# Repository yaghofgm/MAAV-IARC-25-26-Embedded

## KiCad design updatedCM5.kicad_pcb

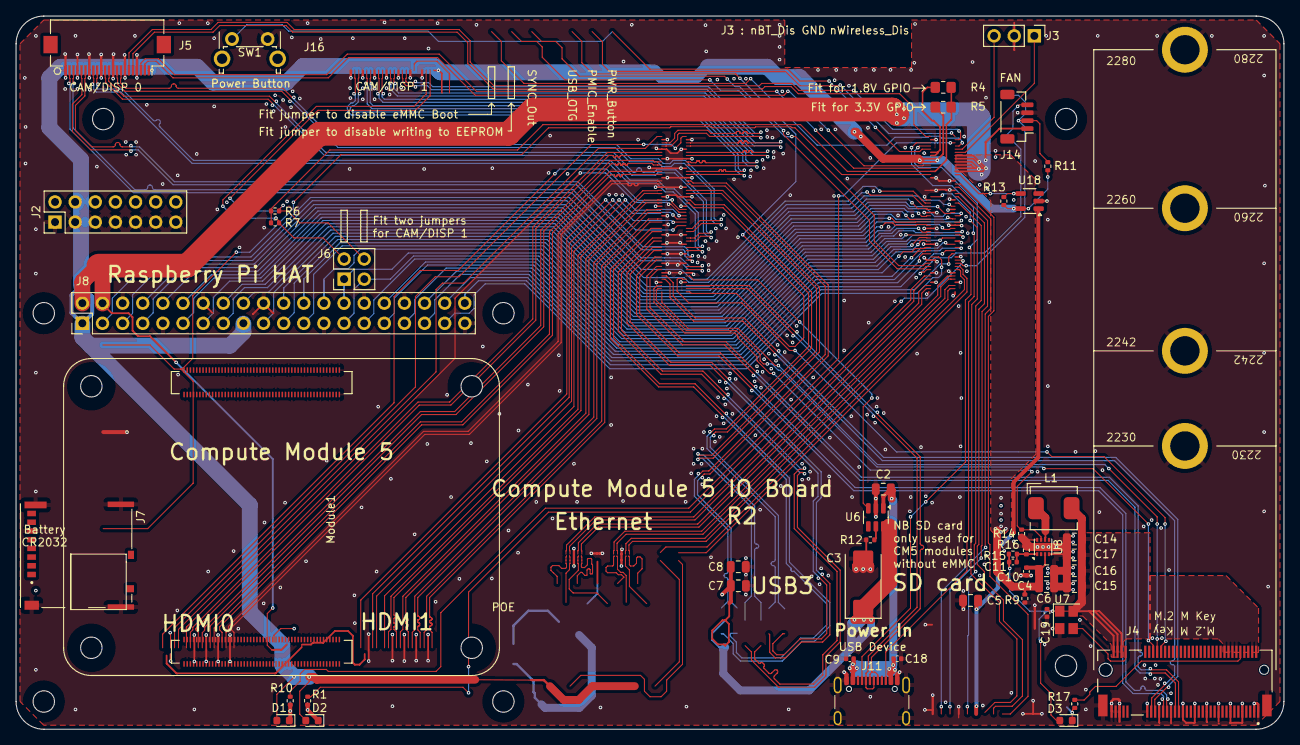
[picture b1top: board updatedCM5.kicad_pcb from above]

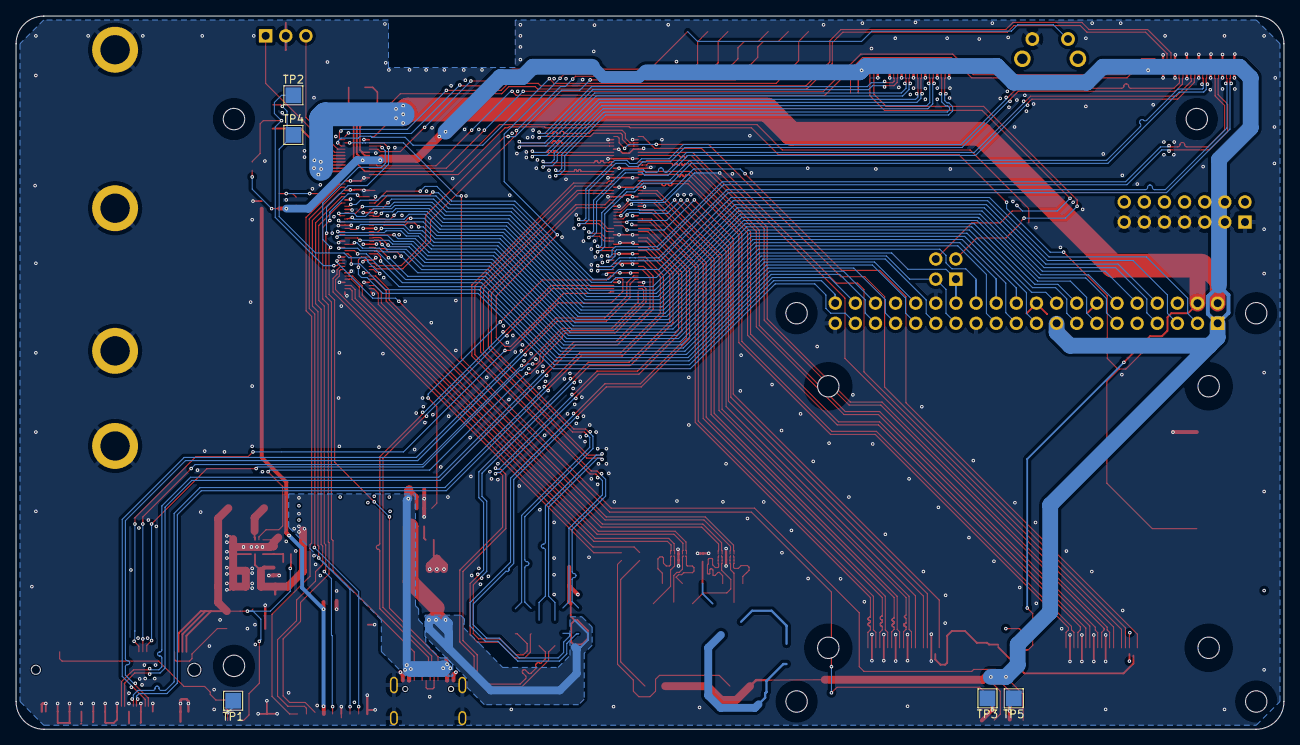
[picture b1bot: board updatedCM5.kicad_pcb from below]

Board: 4 copper layers, 160.0 x 90.0 mm, 61 parts (5 on the bottom side), 94 nets.

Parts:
C2, C4, C5, C6, C7, C8, C14, C15, C16, C17: 10u; C_0805_2012Metric
C3: 100uF; CP_EIA-7343-31_Kemet-D
C9, C10, C18, C19: 100n; C_0402_1005Metric
C11: 4.7nF; C_0402_1005Metric
D1: LED Red; LED_0603_1608Metric
D2, D3: LED Green; LED_0603_1608Metric
H2, H3, H4, H5, H6, H7, H8: MountingHole; MountingHole_2.7mm_M2.5_DIN965
J2: Conn_02x07_Odd_Even; PinHeader_2x07_P2.54mm_Vertical
J3: Conn_01x03; PinHeader_1x03_P2.54mm_Vertical
J4: Bus_M.2_Socket_M; M.2 M Key socket
J5: Conn_01x22_Female; Hirose_FH12-22S-0.5SH_1x22-1MP_P0.50mm_Horizontal
J6: THD-02-R; PinHeader_2x02_P2.54mm_Vertical
J7: Micro_SD_Card_Det; SDCARD_MOLEX_503398-1892
J8: THD-20-R; PinHeader_2x20_P2.54mm_Vertical
J11: USB_C_Receptacle_USB2.0; USB_C_Receptacle_GCT_USB4105-xx-A_16P_TopMnt_Horizontal
J14: JST_SHBM04B-SRSS-TB; JST_SH_BM04B-SRSS-TB_1x04-1MP_P1.00mm_Vertical
L1: 2.2uH; L_Bourns_SRP5030CC
Module1: ComputeModule5-CM5; Raspberry-Pi-5-Compute-Module
R1, R10, R17: 1k; R_0402_1005Metric
R4: nf; R_0805_2012Metric_Pad1.20x1.40mm_HandSolder
R5: 0R; R_0805_2012Metric_Pad1.20x1.40mm_HandSolder
R6, R7, R9, R16: 2.2K 1%; R_0402_1005Metric
R11, R13, R15: 10K 1%; R_0402_1005Metric
R12: 15K 1%; R_0402_1005Metric
R14: 100K 1%; R_0402_1005Metric
SW1: Right angle Tact button; SW_Tactile_SPST_Angled_PTS645Vx58-2LFS
TP1, TP2, TP3, TP4, TP5: TestPoint; TestPoint_Pad_2.0x2.0mm
U6: AP22653W6; SOT-23-6
U7: ASEK-32.768KHZ-L-R-T; Crystal_SMD_3225-4Pin_3.2x2.5mm
U8: AP3441SHE-7B; DFN-8-1EP_2x2mm_P0.5mm_EP1.05x1.75mm
U18: RT9742GGJ5; SOT-23-5

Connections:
/+3.3v: D1.2 (A), D2.2 (A), J5.22, J8.1, J8.17, Module1.84 (+3.3v_(Output)), Module1.86 (+3.3v_(Output)), R5.1, R11.1, R13.1, U18.5 (IN)
/+5v: C2.1, C4.1, C6.1, C9.1, C10.1, C18.1, J8.2, J8.4, J11.A4 (VBUS), J11.A9 (VBUS), J11.B4 (VBUS), J11.B9 (VBUS), J14.1, Module1.77 (+5v_(Input)), Module1.79 (+5v_(Input)), Module1.81 (+5v_(Input)), Module1.83 (+5v_(Input)), Module1.85 (+5v_(Input)), Module1.87 (+5v_(Input)), R9.1, U6.1 (IN), U8.3 (VIN)
/CC1: J11.A5 (CC1), Module1.94 (CC1)
/CC2: J11.B5 (CC2), Module1.96 (CC2)
/CM5_GPIO ( Ethernet, GPIO, SDCARD)/+1.8v: Module1.88 (+1.8v_(Output)), Module1.90 (+1.8v_(Output)), R4.1
/CM5_GPIO ( Ethernet, GPIO, SDCARD)/BT_nDis: J3.3, Module1.91 (BT_nDisable)
/CM5_GPIO ( Ethernet, GPIO, SDCARD)/CAM_GPIO0: J5.17, Module1.97 (CAM_GPIO0)
/CM5_GPIO ( Ethernet, GPIO, SDCARD)/CAM_GPIO1: J5.18, Module1.100 (CAM_GPIO1)
/CM5_GPIO ( Ethernet, GPIO, SDCARD)/EEPROM_nWP: J2.4, Module1.20 (EEPROM_nWP)
/CM5_GPIO ( Ethernet, GPIO, SDCARD)/GPIO2: J8.3, Module1.58 (GPIO2)
/CM5_GPIO ( Ethernet, GPIO, SDCARD)/GPIO3: J8.5, Module1.56 (GPIO3)
/CM5_GPIO ( Ethernet, GPIO, SDCARD)/GPIO4: J8.7, Module1.54 (GPIO4)
/CM5_GPIO ( Ethernet, GPIO, SDCARD)/GPIO5: J8.29, Module1.34 (GPIO5)
/CM5_GPIO ( Ethernet, GPIO, SDCARD)/GPIO6: J8.31, Module1.30 (GPIO6)
/CM5_GPIO ( Ethernet, GPIO, SDCARD)/GPIO7: J8.26, Module1.37 (GPIO7)
/CM5_GPIO ( Ethernet, GPIO, SDCARD)/GPIO8: J8.24, Module1.39 (GPIO8)
/CM5_GPIO ( Ethernet, GPIO, SDCARD)/GPIO9: J8.21, Module1.40 (GPIO9)
/CM5_GPIO ( Ethernet, GPIO, SDCARD)/GPIO10: J8.19, Module1.44 (GPIO10)
/CM5_GPIO ( Ethernet, GPIO, SDCARD)/GPIO11: J8.23, Module1.38 (GPIO11)
/CM5_GPIO ( Ethernet, GPIO, SDCARD)/GPIO12: J8.32, Module1.31 (GPIO12)
/CM5_GPIO ( Ethernet, GPIO, SDCARD)/GPIO13: J8.33, Module1.28 (GPIO13)
/CM5_GPIO ( Ethernet, GPIO, SDCARD)/GPIO14: J8.8, Module1.55 (GPIO14)
/CM5_GPIO ( Ethernet, GPIO, SDCARD)/GPIO15: J8.10, Module1.51 (GPIO15)
/CM5_GPIO ( Ethernet, GPIO, SDCARD)/GPIO16: J8.36, Module1.29 (GPIO16)
/CM5_GPIO ( Ethernet, GPIO, SDCARD)/GPIO17: J8.11, Module1.50 (GPIO17)
/CM5_GPIO ( Ethernet, GPIO, SDCARD)/GPIO18: J8.12, Module1.49 (GPIO18)
/CM5_GPIO ( Ethernet, GPIO, SDCARD)/GPIO19: J8.35, Module1.26 (GPIO19)
/CM5_GPIO ( Ethernet, GPIO, SDCARD)/GPIO20: J8.38, Module1.27 (GPIO20)
/CM5_GPIO ( Ethernet, GPIO, SDCARD)/GPIO21: J8.40, Module1.25 (GPIO21)
/CM5_GPIO ( Ethernet, GPIO, SDCARD)/GPIO22: J8.15, Module1.46 (GPIO22)
/CM5_GPIO ( Ethernet, GPIO, SDCARD)/GPIO23: J8.16, Module1.47 (GPIO23)
/CM5_GPIO ( Ethernet, GPIO, SDCARD)/GPIO24: J8.18, Module1.45 (GPIO24)
/CM5_GPIO ( Ethernet, GPIO, SDCARD)/GPIO25: J8.22, Module1.41 (GPIO25)
/CM5_GPIO ( Ethernet, GPIO, SDCARD)/GPIO26: J8.37, Module1.24 (GPIO26)
/CM5_GPIO ( Ethernet, GPIO, SDCARD)/GPIO27: J8.13, Module1.48 (GPIO27)
/CM5_GPIO ( Ethernet, GPIO, SDCARD)/GPIO_VREF: Module1.78 (GPIO_VREF(1.8v/3.3v_Input)), R4.2, R5.2, R6.1, R7.1
/CM5_GPIO ( Ethernet, GPIO, SDCARD)/ID_SC: J6.1, J8.28, Module1.35 (ID_SC)
/CM5_GPIO ( Ethernet, GPIO, SDCARD)/ID_SD: J6.3, J8.27, Module1.36 (ID_SD)
/CM5_GPIO ( Ethernet, GPIO, SDCARD)/PMIC_ENABLE: J2.12, Module1.99 (PMIC_ENABLE)
/CM5_GPIO ( Ethernet, GPIO, SDCARD)/PWM: J14.2, Module1.19 (FAN_PWM), R11.2, TP2.1
/CM5_GPIO ( Ethernet, GPIO, SDCARD)/PWR_BUT: J2.14, Module1.92 (PWR_BUT), SW1.1
/CM5_GPIO ( Ethernet, GPIO, SDCARD)/SD_CLK: J7.5 (CLK), Module1.57 (SD_CLK)
/CM5_GPIO ( Ethernet, GPIO, SDCARD)/SD_CMD: J7.3 (CMD), Module1.62 (SD_CMD)
/CM5_GPIO ( Ethernet, GPIO, SDCARD)/SD_DAT0: J7.7 (DAT0), Module1.63 (SD_DAT0)
/CM5_GPIO ( Ethernet, GPIO, SDCARD)/SD_DAT1: J7.8 (DAT1), Module1.67 (SD_DAT1)
/CM5_GPIO ( Ethernet, GPIO, SDCARD)/SD_DAT2: J7.1 (DAT2), Module1.69 (SD_DAT2)
/CM5_GPIO ( Ethernet, GPIO, SDCARD)/SD_DAT3: J7.2 (DAT3/CD), Module1.61 (SD_DAT3)
/CM5_GPIO ( Ethernet, GPIO, SDCARD)/SD_PWR: C5.1, J7.4 (VDD), U18.1 (OUT)
/CM5_GPIO ( Ethernet, GPIO, SDCARD)/SD_PWR_ON: Module1.75 (SD_PWR_ON), R13.2, U18.4 (EN)
/CM5_GPIO ( Ethernet, GPIO, SDCARD)/SYNC_OUT: J2.6, Module1.18 (Ethernet_SYNC_OUT(3.3v))
/CM5_GPIO ( Ethernet, GPIO, SDCARD)/TACHO: J14.4, Module1.16 (FAN_TACHO), TP4.1
/CM5_GPIO ( Ethernet, GPIO, SDCARD)/USBOTG: J2.10, Module1.101 (USB_OTG_ID)
/CM5_GPIO ( Ethernet, GPIO, SDCARD)/WL_nDis: J3.1, Module1.89 (WiFi_nDisable)
/CM5_GPIO ( Ethernet, GPIO, SDCARD)/nPWR_LED: Module1.95 (LED_nPWR), R10.2
/CM5_GPIO ( Ethernet, GPIO, SDCARD)/nRPIBOOT: J2.2, Module1.93 (nRPIBOOT)
/CM5_HighSpeed/DPHY0_C_N: J5.8, Module1.127 (MIPI0_C_N)
/CM5_HighSpeed/DPHY0_C_P: J5.9, Module1.129 (MIPI0_C_P)
/CM5_HighSpeed/DPHY0_D0_N: J5.2, Module1.115 (MIPI0_D0_N)
/CM5_HighSpeed/DPHY0_D0_P: J5.3, Module1.117 (MIPI0_D0_P)
/CM5_HighSpeed/DPHY0_D1_N: J5.5, Module1.121 (MIPI0_D1_N)
/CM5_HighSpeed/DPHY0_D1_P: J5.6, Module1.123 (MIPI0_D1_P)
/CM5_HighSpeed/DPHY0_D2_N: J5.11, Module1.133 (MIPI0_D2_N)
/CM5_HighSpeed/DPHY0_D2_P: J5.12, Module1.135 (MIPI0_D2_P)
/CM5_HighSpeed/DPHY0_D3_N: J5.14, Module1.139 (MIPI0_D3_N)
/CM5_HighSpeed/DPHY0_D3_P: J5.15, Module1.141 (MIPI0_D3_P)
/CM5_HighSpeed/PCIE_CLK_N: J4.53 (REFCLKn), Module1.112 (PCIe_CLK_N)
/CM5_HighSpeed/PCIE_CLK_P: J4.55 (REFCLKp), Module1.110 (PCIe_CLK_P)
/CM5_HighSpeed/PCIE_PWR_EN: Module1.106 (PCIE_PWR_EN), R14.1, U8.7 (EN)
/CM5_HighSpeed/PCIE_RX_N: J4.43 (PETp0), Module1.118 (PCIe_RX_N)
/CM5_HighSpeed/PCIE_RX_P: J4.41 (PETn0), Module1.116 (PCIe_RX_P)
/CM5_HighSpeed/PCIE_TX_N: J4.49 (PERp0), Module1.124 (PCIe_TX_N)
/CM5_HighSpeed/PCIE_TX_P: J4.47 (PERn0), Module1.122 (PCIe_TX_P)
/CM5_HighSpeed/PCIE_nCLKREQ: J4.52 (~CLKREQ), Module1.102 (PCIe_nCLKREQ)
/CM5_HighSpeed/PCIE_nRST: J4.50 (~PERST), Module1.109 (PCIe_nRST)
/CM5_HighSpeed/PCIE_nWAKE: J4.54 (~PEWAKE), Module1.104 (PCIE_nWAKE)
/CM5_HighSpeed/SCL0: J5.20, Module1.80 (SCL0)
/CM5_HighSpeed/SCL1: J6.2, R7.2
/CM5_HighSpeed/SDA0: J5.21, Module1.82 (SDA0)
/CM5_HighSpeed/SDA1: J6.4, R6.2
/CM5_HighSpeed/VBUS: C3.1, C7.1, C8.1, U6.6 (OUT)
/CM5_HighSpeed/VBUS_EN: Module1.111 (VBUS_EN), U6.3 (EN)
/PCIe-M2/FB: C11.2, R15.2, R16.1, U8.1 (FB)
/PCIe-M2/M2_3v3: C11.1, C14.1, C15.1, C16.1, C17.1, C19.1, D3.2 (A), J4.2 (3.3V), J4.4 (3.3V), J4.12 (3.3V), J4.14 (3.3V), J4.16 (3.3V), J4.18 (3.3V), J4.70 (3.3V), J4.72 (3.3V), J4.74 (3.3V), L1.2, R15.1, U7.1 (EN), U7.4 (VDD)
/USB2_N: J11.A7 (D-), J11.B7 (D-), Module1.103 (USB2_N)
/USB2_P: J11.A6 (D+), J11.B6 (D+), Module1.105 (USB2_P)
GND: C2.2, C3.2, C4.2, C5.2, C6.2, C7.2, C8.2, C9.2, C10.2, C14.2, C15.2, C16.2, C17.2, C18.2, C19.2, J2.1, J2.3, J2.5, J2.7, J2.9, J2.11, J2.13, J3.2, J4.1 (GND), J4.3 (GND), J4.9 (GND), J4.15 (GND), J4.21 (GND), J4.27 (GND), J4.33 (GND), J4.39 (GND), J4.45 (GND), J4.51 (GND), J4.57 (GND), J4.71 (GND), J4.73 (GND), J4.75 (GND), J4.M1 (GND2230), J4.M2 (GND2242), J4.M3 (GND2260), J4.M4 (GND2280), J4.S1, J4.S2, J5.1, J5.4, J5.7, J5.10, J5.13, J5.16, J5.19, J7.6 (VSS), J7.11 (SHIELD), J8.6, J8.9, J8.14, J8.20, J8.25, J8.30, J8.34, J8.39, J11.A1 (GND), J11.A12 (GND), J11.B1 (GND), J11.B12 (GND), J11.S1 (SHIELD), J14.3, Module1.1 (GND), Module1.2 (GND), Module1.7 (GND), Module1.8 (GND), Module1.13 (GND), Module1.14 (GND), Module1.22 (GND), Module1.23 (GND), Module1.32 (GND), Module1.33 (GND), Module1.42 (GND), Module1.43 (GND), Module1.52 (GND), Module1.53 (GND), Module1.59 (GND), Module1.60 (GND), Module1.65 (GND), Module1.66 (GND), Module1.71 (GND), Module1.74 (GND), Module1.98 (GND), Module1.107 (GND), Module1.108 (GND), Module1.113 (GND), Module1.114 (GND), Module1.119 (GND), Module1.120 (GND), Module1.125 (GND), Module1.126 (GND), Module1.131 (GND), Module1.132 (GND), Module1.137 (GND), Module1.138 (GND), Module1.144 (GND), Module1.150 (GND), Module1.155 (GND), Module1.156 (GND), Module1.161 (GND), Module1.162 (GND), Module1.167 (GND), Module1.168 (GND), Module1.173 (GND), Module1.174 (GND), Module1.179 (GND), Module1.180 (GND), Module1.185 (GND), Module1.186 (GND), Module1.191 (GND), Module1.192 (GND), Module1.197 (GND), Module1.198 (GND), R9.2, R12.2, R14.2, R16.2, SW1.2, U6.2 (GND), U7.2 (GND), U8.4 (PGND), U8.8 (SGND), U8.9 (PAD), U18.2 (GND)
unnamed: D1.1 (K), R10.1, TP5.1
unnamed: D2.1 (K), R1.1, TP3.1
unnamed: D3.1 (K), R17.1, TP1.1
unnamed: J4.10 (DAS/~DSS/~LED1), R17.2
unnamed: J4.68 (SUSCLK), U7.3 (Out)
unnamed: Module1.21 (LED_nACT), R1.2
unnamed: R12.1, U6.5 (ILIM)
unnamed: L1.1, U8.6 (LX)

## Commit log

2026-01-11 initial
2026-01-11 some no connects
2026-01-11 end of jan 11th
2026-01-13 Removed PCIE connector and fixed ERC errors
2026-01-13 Removed ERC errors and M2 connector
2026-01-13 Clean repo: remove autosaves/backups, update KiCad files
